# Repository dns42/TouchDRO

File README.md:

Use at your own risk.
This thing is completely untested yet.

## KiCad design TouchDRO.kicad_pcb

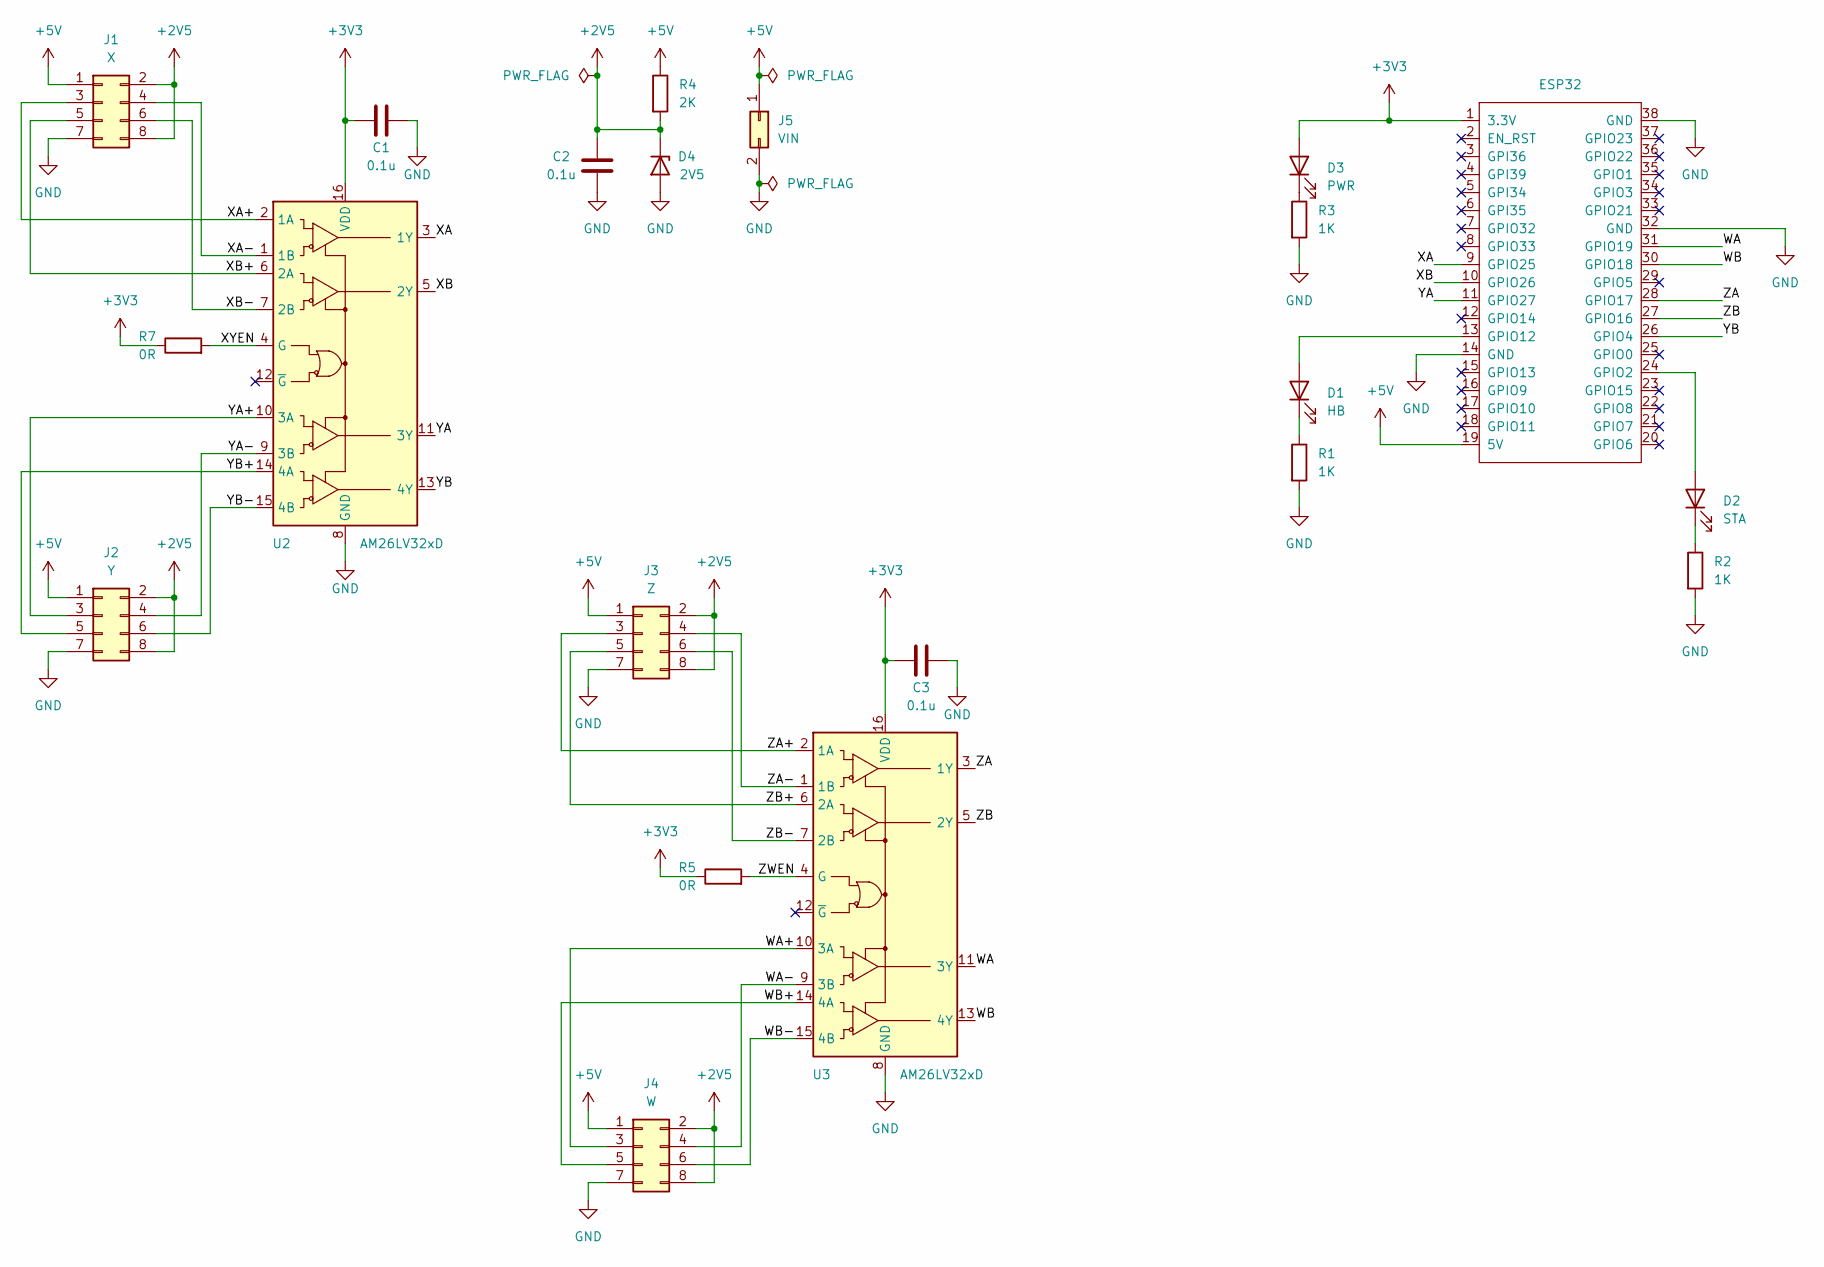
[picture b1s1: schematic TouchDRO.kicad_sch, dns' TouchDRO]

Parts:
C1, C2, C3: 0.1u; C_0805_2012Metric
D1: HB; LED_0805_2012Metric
D2: STA; LED_0805_2012Metric
D3: PWR; LED_0805_2012Metric
D4: 2V5; D_0805_2012Metric
ESP32: ESP32; ESP32-38Pin
J1: X; PinHeader_2x04_P2.54mm_Vertical
J2: Y; PinHeader_2x04_P2.54mm_Vertical
J3: Z; PinHeader_2x04_P2.54mm_Vertical
J4: W; PinHeader_2x04_P2.54mm_Vertical
J5: VIN; PinHeader_1x02_P2.54mm_Vertical
R1, R2, R3: 1K; R_0603_1608Metric
R4: 2K; R_0603_1608Metric
R5, R7: 0R; SolderJumper-2_P1.3mm_Bridged_RoundedPad1.0x1.5mm
U2, U3: AM26LV32xD; SOIC-16_3.9x9.9mm_P1.27mm

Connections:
+2V5: C2.2, D4.1 (K), J1.2, J1.8, J2.2, J2.8, J3.2, J3.8, J4.2, J4.8, R4.2
+3V3: C1.1, C3.1, D3.2 (A), ESP32.1 (3.3V), R5.1, R7.1, U2.16 (VDD), U3.16 (VDD)
+5V: ESP32.19 (5V), J1.1, J2.1, J3.1, J4.1, J5.1, R4.1
/WA: ESP32.31 (GPIO19), U3.11 (3Y)
/WA+: J4.3, U3.10 (3A)
/WA-: J4.4, U3.9 (3B)
/WB: ESP32.30 (GPIO18), U3.13 (4Y)
/WB+: J4.5, U3.14 (4A)
/WB-: J4.6, U3.15 (4B)
/XA: ESP32.9 (GPIO25), U2.3 (1Y)
/XA+: J1.3, U2.2 (1A)
/XA-: J1.4, U2.1 (1B)
/XB: ESP32.10 (GPIO26), U2.5 (2Y)
/XB+: J1.5, U2.6 (2A)
/XB-: J1.6, U2.7 (2B)
/XYEN: R7.2, U2.4 (G)
/YA: ESP32.11 (GPIO27), U2.11 (3Y)
/YA+: J2.3, U2.10 (3A)
/YA-: J2.4, U2.9 (3B)
/YB: ESP32.26 (GPIO4), U2.13 (4Y)
/YB+: J2.5, U2.14 (4A)
/YB-: J2.6, U2.15 (4B)
/ZA: ESP32.28 (GPIO17), U3.3 (1Y)
/ZA+: J3.3, U3.2 (1A)
/ZA-: J3.4, U3.1 (1B)
/ZB: ESP32.27 (GPIO16), U3.5 (2Y)
/ZB+: J3.5, U3.6 (2A)
/ZB-: J3.6, U3.7 (2B)
/ZWEN: R5.2, U3.4 (G)
GND: C1.2, C2.1, C3.2, D4.2 (A), ESP32.14 (GND), ESP32.32 (GND), ESP32.38 (GND), J1.7, J2.7, J3.7, J4.7, J5.2, R1.2, R2.2, R3.2, U2.8 (GND), U3.8 (GND)
unnamed: D1.2 (A), ESP32.13 (GPIO12)
unnamed: D1.1 (K), R1.1
unnamed: D2.2 (A), ESP32.24 (GPIO2)
unnamed: D2.1 (K), R2.1
unnamed: D3.1 (K), R3.1

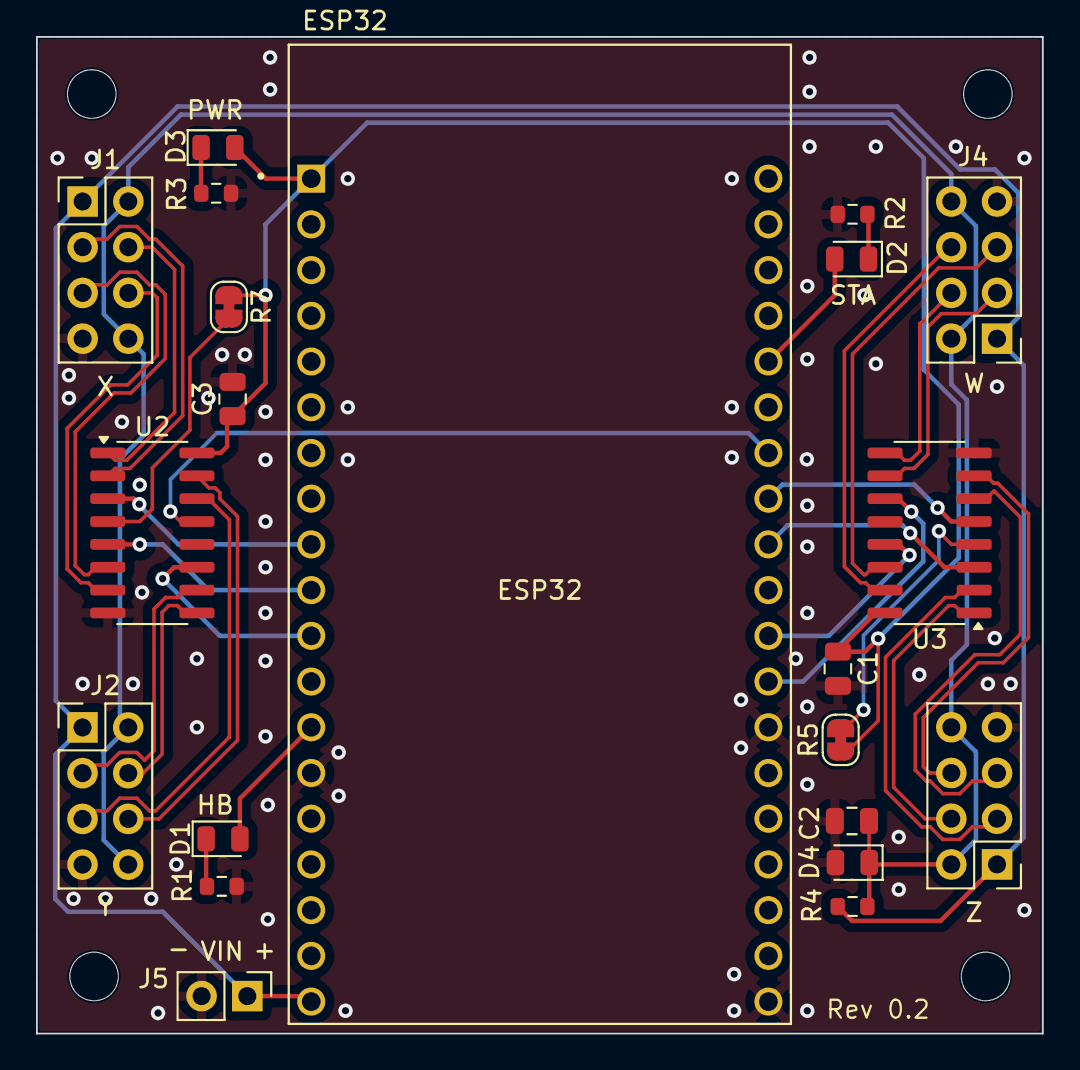
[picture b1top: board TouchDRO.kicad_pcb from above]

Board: 2 copper layers, 55.9 x 55.4 mm, 21 parts (0 on the bottom side), 35 nets.

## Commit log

2025-02-23 v0.1
2025-02-23 v0.1: add Top/Bottom.png to gbr
2025-03-14 v0.2
